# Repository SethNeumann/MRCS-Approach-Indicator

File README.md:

# REPO NAME: EagleTemplate-new
## License: Creative Commons Attribution-NonCommercial-ShareAlike

The approach indicator supports up to 4 stations, each with 2 sensors on each side (that is an East home, East distant and West Home West distant).  THese are optical
sensors connected to analog inputs of the Arduino Nano.  By checking the sequence in which the sensors are covered the sketch (by Jon Schmidt) sets a directional stick
and only fires it's output (relay contact closure) on inbound trains.  The Arduino monitors ambient light and continuously re-calibrates.  An additional two stations are
provided with digital inputs, the user supplies complete detector units such as the MRCS EOPD or EOPDx4 for train detection.

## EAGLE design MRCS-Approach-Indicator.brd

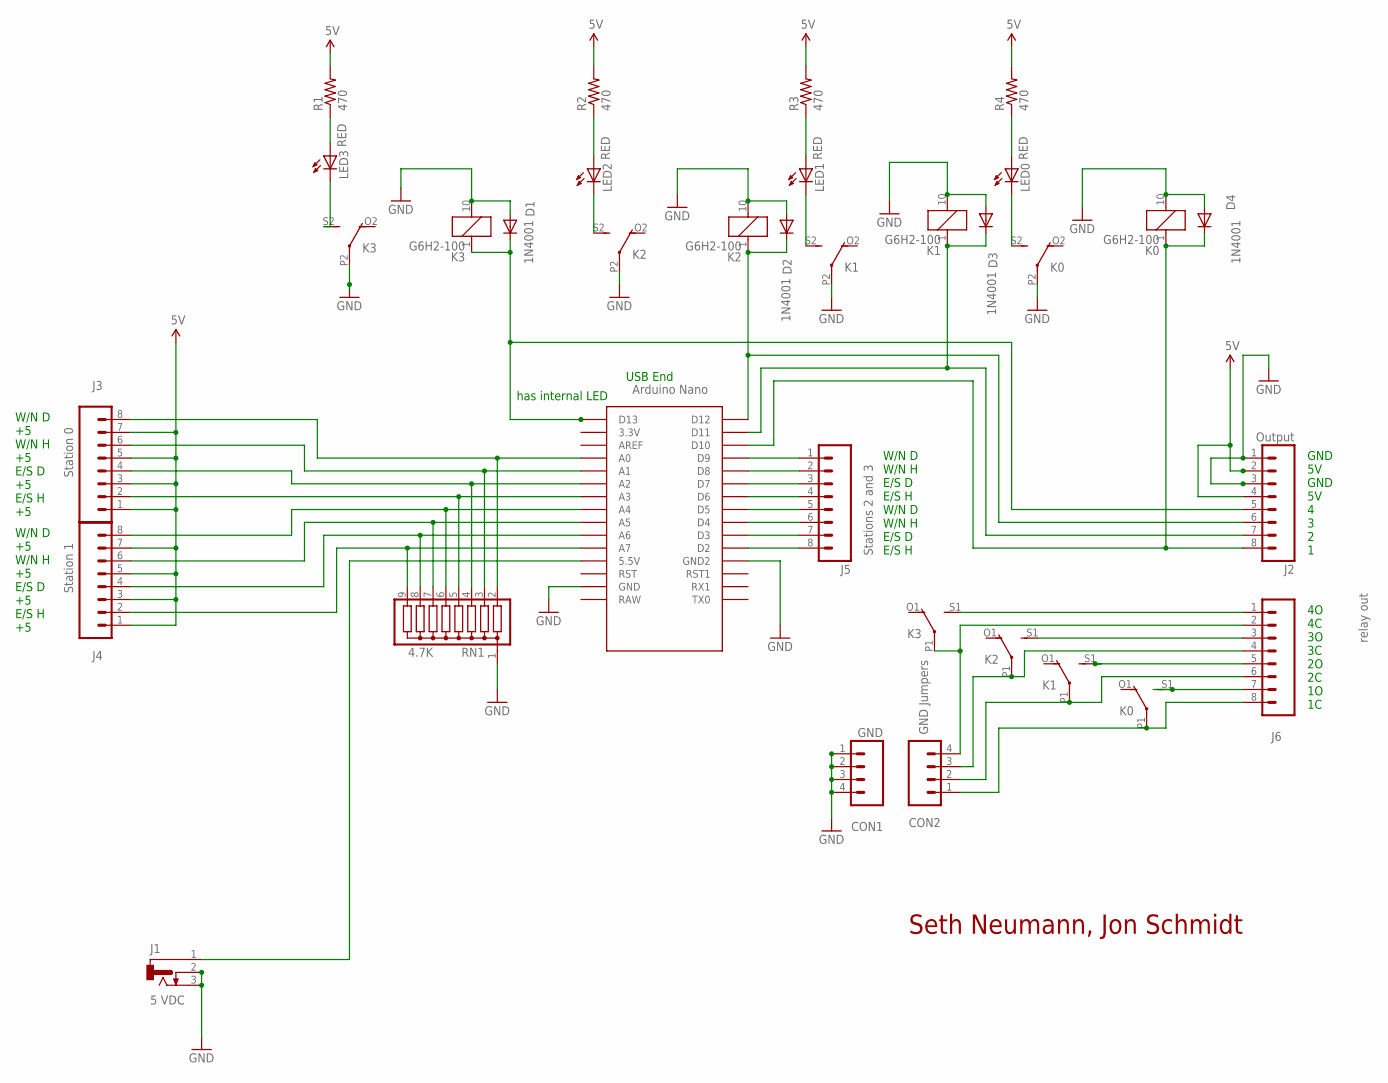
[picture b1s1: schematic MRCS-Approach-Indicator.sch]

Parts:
CON1: GND; 1X04_LOCK
CON2: GND Jumpers; 1X04_LOCK
D1, D2, D3, D4: 1N4001; DIODE-1N4001
J1: 5 VDC; DCJ0202
J2: Output; 1X08_LOCK
J3: Station 0; 1X08_LOCK
J4: Station 1; 1X08_LOCK
J5: Stations 2 and 3; 1X08_LOCK
J6: relay out; 1X08_LOCK
K0, K1, K2, K3: G6H2-100
LED0, LED1, LED2, LED3: RED; LED3MM
NANO: NANO
R1, R2, R3, R4: 470; AXIAL-0.4-RES
RN1: 4.7K; SIL9

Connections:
5V: J1.1, J2.2, J2.4, J3.1, J3.3, J3.5, J3.7, J4.1, J4.3, J4.5, J4.7, NANO.5V (5.5V), R1.P$2 (2), R2.P$2 (2), R3.P$2 (2), R4.P$2 (2)
D7: D1.C, J2.5, K3.1, NANO.D13
D12: D2.C, J2.6, K2.1, NANO.D12
GND: CON1.1, CON1.2, CON1.3, CON1.4, D1.A, D2.A, D3.A, D4.A, J1.2, J1.3, J2.1, J2.3, K0.10 (2), K0.P2, K1.10 (2), K1.P2, K2.10 (2), K2.P2, K3.10 (2), K3.P2, NANO.GND, NANO.GND1 (GND2), RN1.1
unnamed: J6.3, K2.S1 (S)
unnamed: D4.C, J2.8, K0.1, NANO.D10
unnamed: J3.8, NANO.A0, RN1.2
unnamed: J3.6, NANO.A1, RN1.3
unnamed: J3.4, NANO.A2, RN1.4
unnamed: J3.2, NANO.A3, RN1.5
unnamed: J6.1, K3.S1 (S)
unnamed: CON2.3, J6.4, K2.P1
unnamed: J4.8, NANO.A4, RN1.6
unnamed: J4.6, NANO.A5, RN1.7
unnamed: J4.4, NANO.A6, RN1.8
unnamed: J4.2, NANO.A7, RN1.9
unnamed: J5.8, NANO.D2
unnamed: J5.7, NANO.D3
unnamed: J5.6, NANO.D4
unnamed: J5.5, NANO.D5
unnamed: J5.4, NANO.D6
unnamed: J5.3, NANO.D7
unnamed: J5.2, NANO.D8
unnamed: J5.1, NANO.D9
unnamed: J6.5, K1.S1 (S)
unnamed: CON2.4, J6.2, K3.P1
unnamed: CON2.2, J6.6, K1.P1
unnamed: J6.7, K0.S1 (S)
unnamed: CON2.1, J6.8, K0.P1
unnamed: K3.S2 (S), LED3.K (C)
unnamed: LED3.A, R1.P$1 (1)
unnamed: LED2.A, R2.P$1 (1)
unnamed: K2.S2 (S), LED2.K (C)
unnamed: LED1.A, R3.P$1 (1)
unnamed: K1.S2 (S), LED1.K (C)
unnamed: LED0.A, R4.P$1 (1)
unnamed: K0.S2 (S), LED0.K (C)
unnamed: D3.C, J2.7, K1.1, NANO.D11

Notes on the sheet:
has internal LED
GND 5V GND 5V 4 3 2 1
USB End
Seth Neumann, Jon Schmidt
W/N D +5 W/N H +5 E/S D +5 E/S H +5
W/N D W/N H E/S D E/S H W/N D W/N H E/S D E/S H
4O 4C 3O 3C 2O 2C 1O 1C

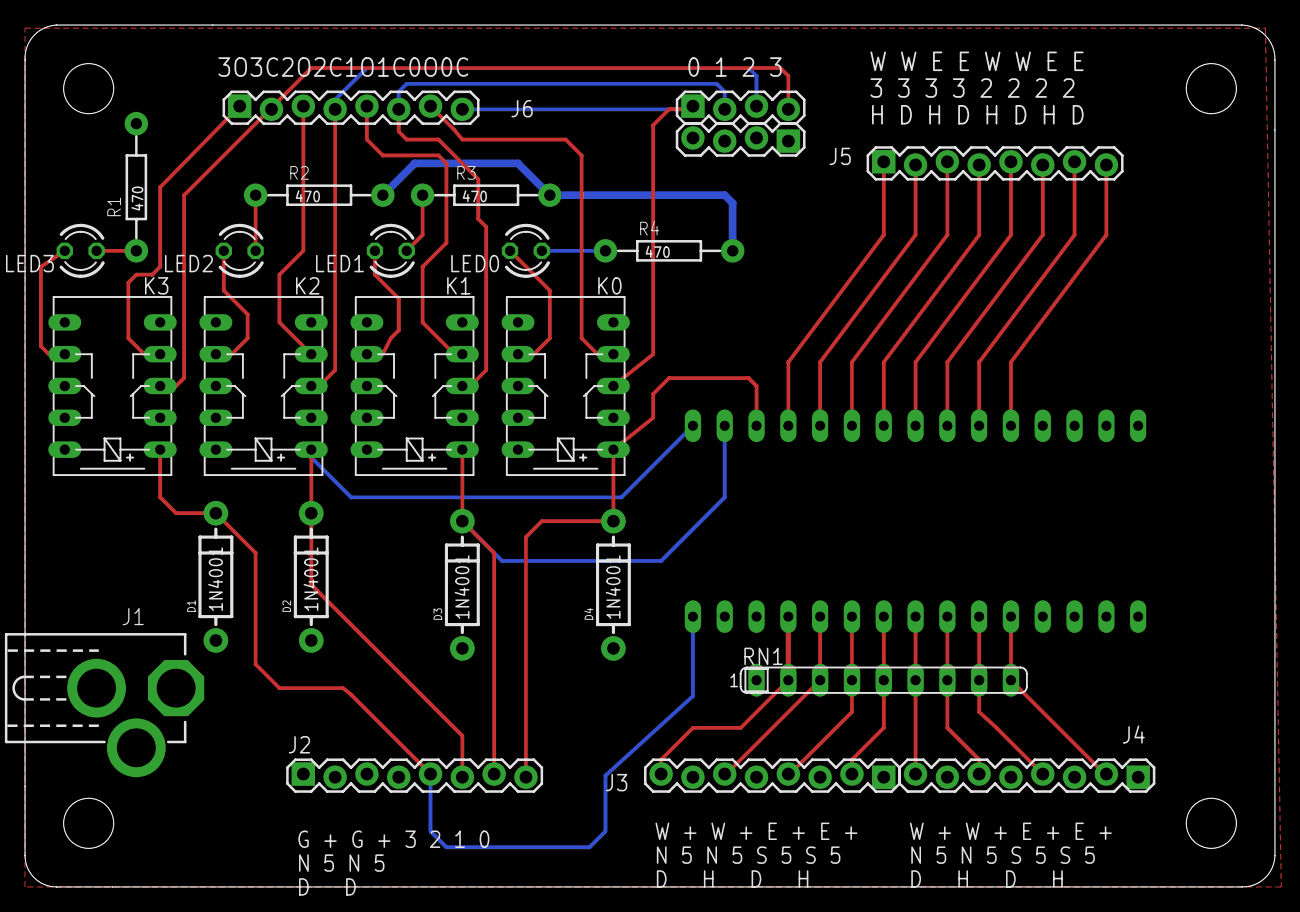
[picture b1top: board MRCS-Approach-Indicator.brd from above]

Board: 2 copper layers, 99.8 x 68.8 mm, 30 parts (0 on the bottom side), 38 nets.

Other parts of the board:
U$1: BOARD-DINRAIL-2.7IN
U$2: MRCSLOGOTOP
U$3: MRCSLOGOBTM
U$5: CA-PROP65WARNING

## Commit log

2021-08-28 moved files from local directory into Github
    brd, sch files as well as pdfs and Jon Schmidt's direction detection sketch for the Nano
2021-08-28 changes after design review
    - changed contacts to dry pairs with grounding jumper
    - added LEDs for relay status
    - re-arranged raw logic outputs and added another +5/GND pair
    - fixed label issues
2021-08-30 Order as submitter to JLCPCB
    Changes after design review with Jon Schmidt, various label clean up items. Thanks to John Plocher for suggestions on managing back side labels and logos!
2021-09-04 Update MRCS-Approach-Indicator Schematic.pdf
    change title to 555 tone generator
2021-09-04 Update MRCS-Approach-Indicator Schematic.pdf
    replace incorrect schematic
2021-09-19 minor label clean up after building prototypes
    changed size and moved some labels so they can be read more easily
2021-09-19 changes reflecting prototype build
    minor labeling changes, updates to layout
2021-12-04 label corrections
    changes to labels to align better with code, note some board designations are different than schematic
2021-12-29 Version 1.1
    Mostly documentation changes on the board. Note that a couple of the labels on the board don't agree with schematic.
2021-12-29 V1.1 updated labels on board
    V1.1 updated labels on board
2022-01-31 Label changes in revision 1.1
    changed labels to make easier for end user to follow
2022-02-08 repository cleanup
2022-02-08 User Assembly and Installation Instructions
    User Assembly and Installation Instructions V0.5
2022-02-08 minor clean up
    lost the relay and LED renumbering in BOM and installation instructions. Jon removed the entire text of the sketch, check this repository for the latest.
2022-04-25 now using joneschmidt's repository

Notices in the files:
parts and their libraries:
SparkFun-Aesthetics: Licensing: CC v3.0 Share-Alike You are welcome to use this library for commercial purposes.
